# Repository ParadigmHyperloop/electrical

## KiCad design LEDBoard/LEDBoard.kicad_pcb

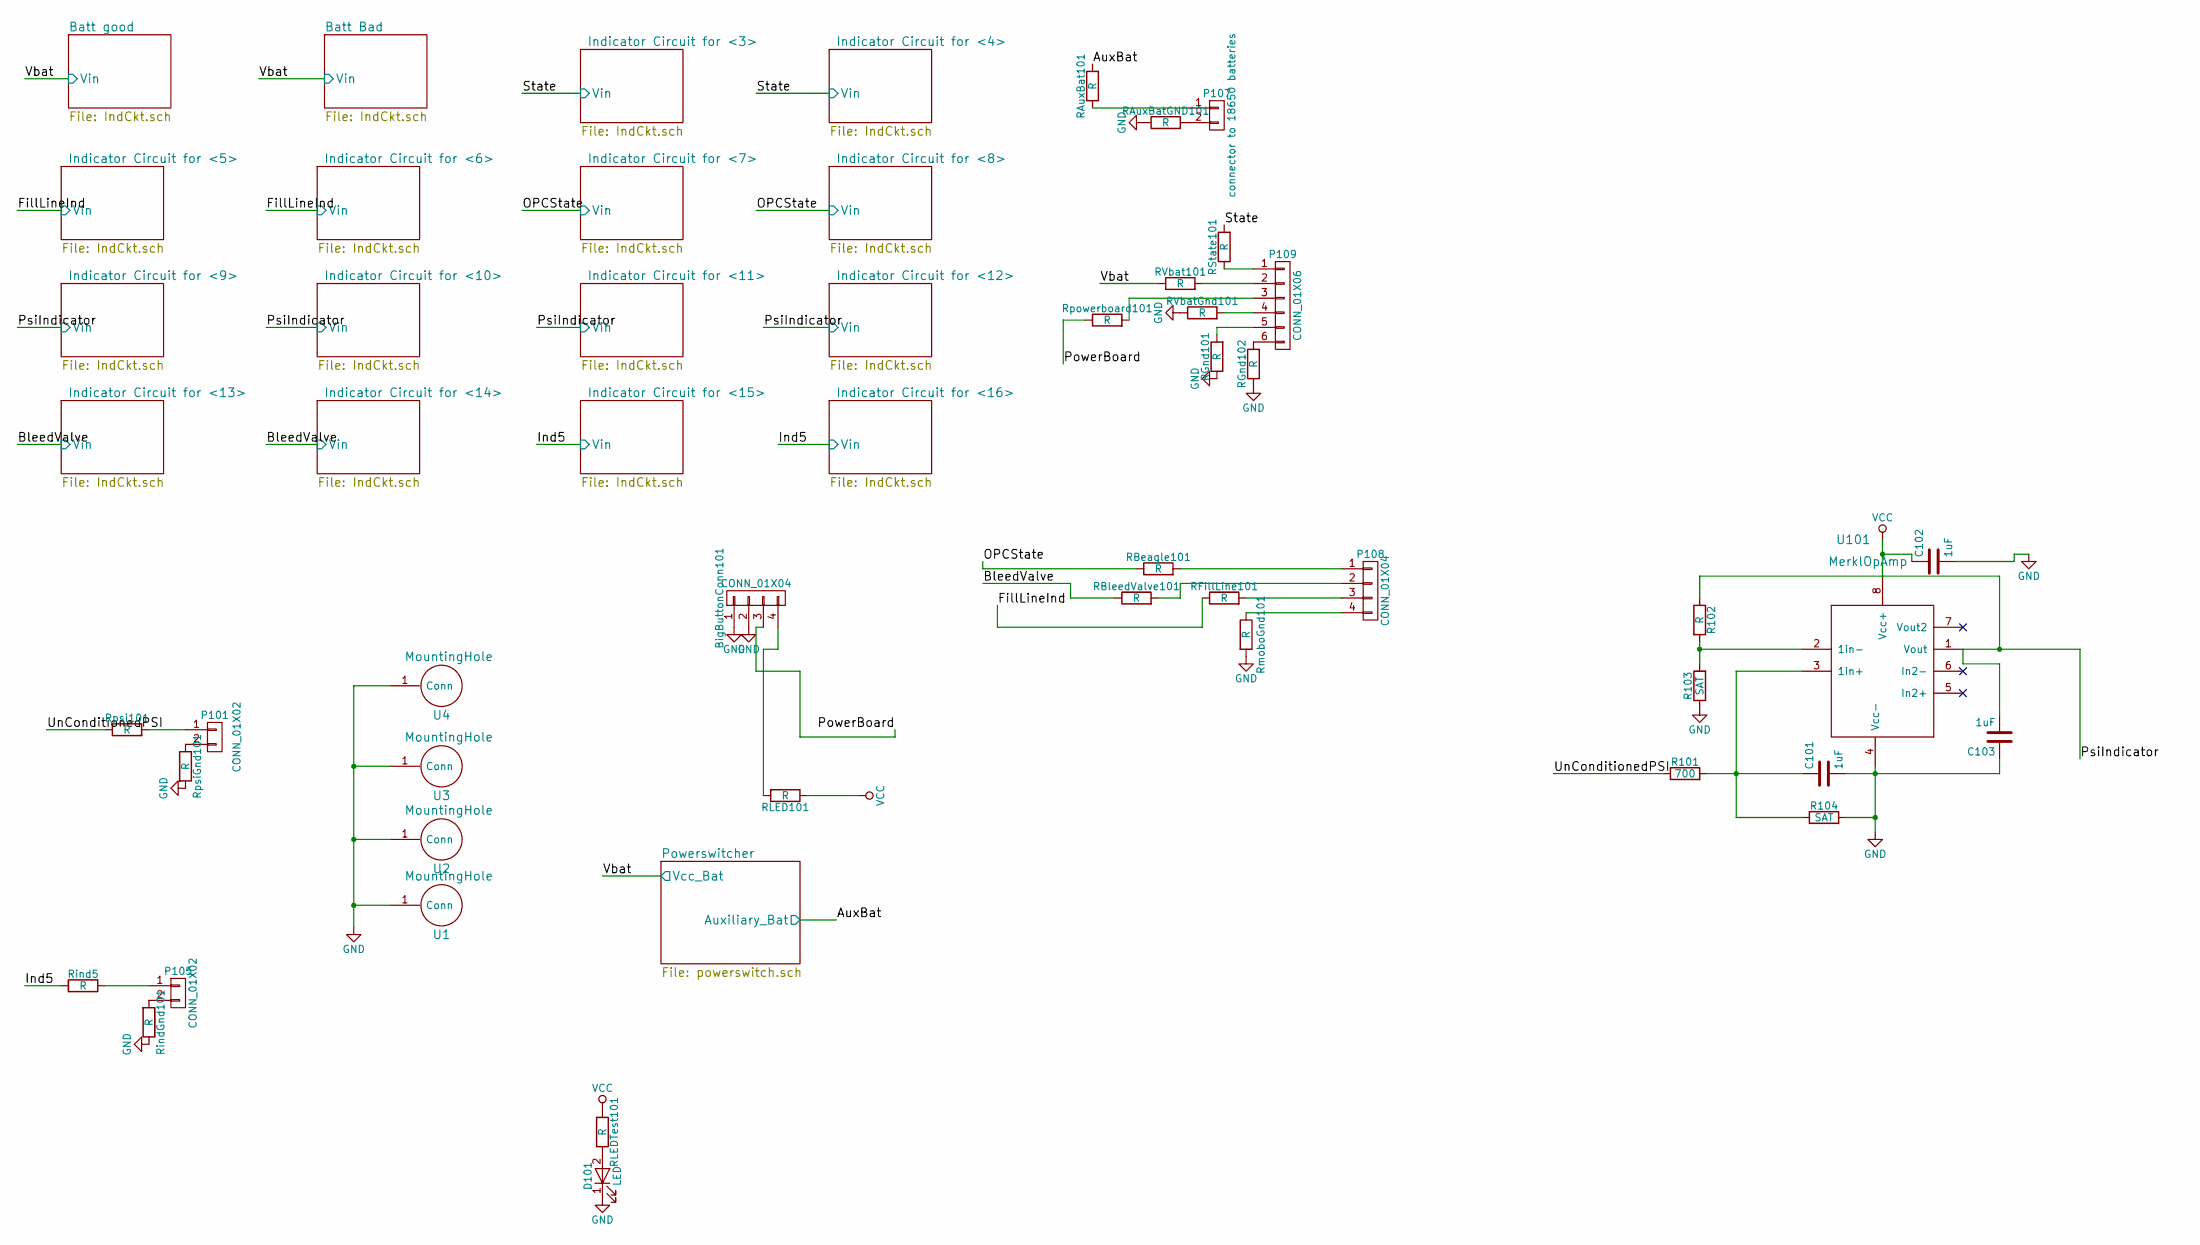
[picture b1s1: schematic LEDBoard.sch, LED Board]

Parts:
BigButtonConn101: CONN_01X04; CONN_PHOENIX_1844236_4PIN_1
C101, C102, C103: 1uF; C_1206_HandSoldering
D101: LED; LED_1206
P101: CONN_01X02; CONN_PHOENIX_1844210_2PIN_1
P105: CONN_01X02; CONN_PHOENIX_1844210_2PIN
P107: connector to 18650 batteries; CONN_PHOENIX_1844210_2PIN
P108: CONN_01X04; CONN_PHOENIX_1844236_4PIN_1
P109: CONN_01X06; CONN_PHOENIX_1844252_6PIN
R101: 700; R_1206_HandSoldering
R102: R; R_1206_HandSoldering
R103, R104: SAT; R_1206_HandSoldering
RAuxBat101: R; R_1206_HandSoldering
RAuxBatGND101: R; R_1206_HandSoldering
RBeagle101: R; R_1206_HandSoldering
RBleedValve101: R; R_1206_HandSoldering
RFillLine101: R; R_1206_HandSoldering
RGnd101, RGnd102: R; R_1206_HandSoldering
RLED101: R; R_1206_HandSoldering
RLEDTest101: R; R_1206_HandSoldering
RState101: R; R_1206_HandSoldering
RVbat101: R; R_1206_HandSoldering
RVbatGnd101: R; R_1206_HandSoldering
Rind5: R; R_1206_HandSoldering
RindGnd101: R; R_1206_HandSoldering
RmoboGnd101: R; R_1206_HandSoldering
Rpowerboard101: R; R_1206_HandSoldering
Rpsi101: R; R_1206_HandSoldering
RpsiGnd101: R; R_1206_HandSoldering
U1, U2, U3, U4: MountingHole; MountingHole_5.5mm_Pad_Via
U101: MerklOpAmp; SOIC-8_3.9x4.9mm_Pitch1.27mm

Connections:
/AuxBat: RAuxBat101.2; also elsewhere on the board
/BleedValve: RBleedValve101.1; also elsewhere on the board
/FillLineInd: RFillLine101.1; also elsewhere on the board
/Ind5: Rind5.2; also elsewhere on the board
/OPCState: RBeagle101.1; also elsewhere on the board
/PowerBoard: BigButtonConn101.3, Rpowerboard101.1
/PsiIndicator: C103.2, R102.1, U101.1 (Vout); also elsewhere on the board
/State: RState101.2; also elsewhere on the board
/UnConditionedPSI: R101.1, Rpsi101.1
/Vbat: RVbat101.1; also elsewhere on the board
GND: BigButtonConn101.1, BigButtonConn101.2, C101.2, C102.2, C103.1, D101.1 (K), R103.1, R104.2, RAuxBatGND101.1, RGnd101.1, RGnd102.1, RVbatGnd101.1, RindGnd101.1, RmoboGnd101.2, RpsiGnd101.2, U1.1, U2.1, U3.1, U4.1, U101.4 (Vcc-); also elsewhere on the board
unnamed: BigButtonConn101.4, RLED101.2
unnamed: C101.1, R101.2, R104.1, U101.3 (1in+)
unnamed 65: D101.2 (A), RLEDTest101.1; also elsewhere on the board
unnamed: P101.1, Rpsi101.2
unnamed: P101.2, RpsiGnd101.1
unnamed: P105.1, Rind5.1
unnamed: P105.2, RindGnd101.2
unnamed: P107.1, RAuxBat101.1
unnamed: P107.2, RAuxBatGND101.2
unnamed: P108.1, RBeagle101.2
unnamed: P108.2, RBleedValve101.2
unnamed: P108.3, RFillLine101.2
unnamed 107: P108.4, RmoboGnd101.1; also elsewhere on the board
unnamed: P109.1, RState101.1
unnamed: P109.2, RVbat101.2
unnamed: P109.3, Rpowerboard101.2
unnamed: P109.4, RVbatGnd101.2
unnamed: P109.5, RGnd101.2
unnamed: P109.6, RGnd102.2
unnamed: R102.2, R103.2, U101.2 (1in-)
VCC: C102.1, RLED101.1, RLEDTest101.2, U101.8 (Vcc+); also elsewhere on the board

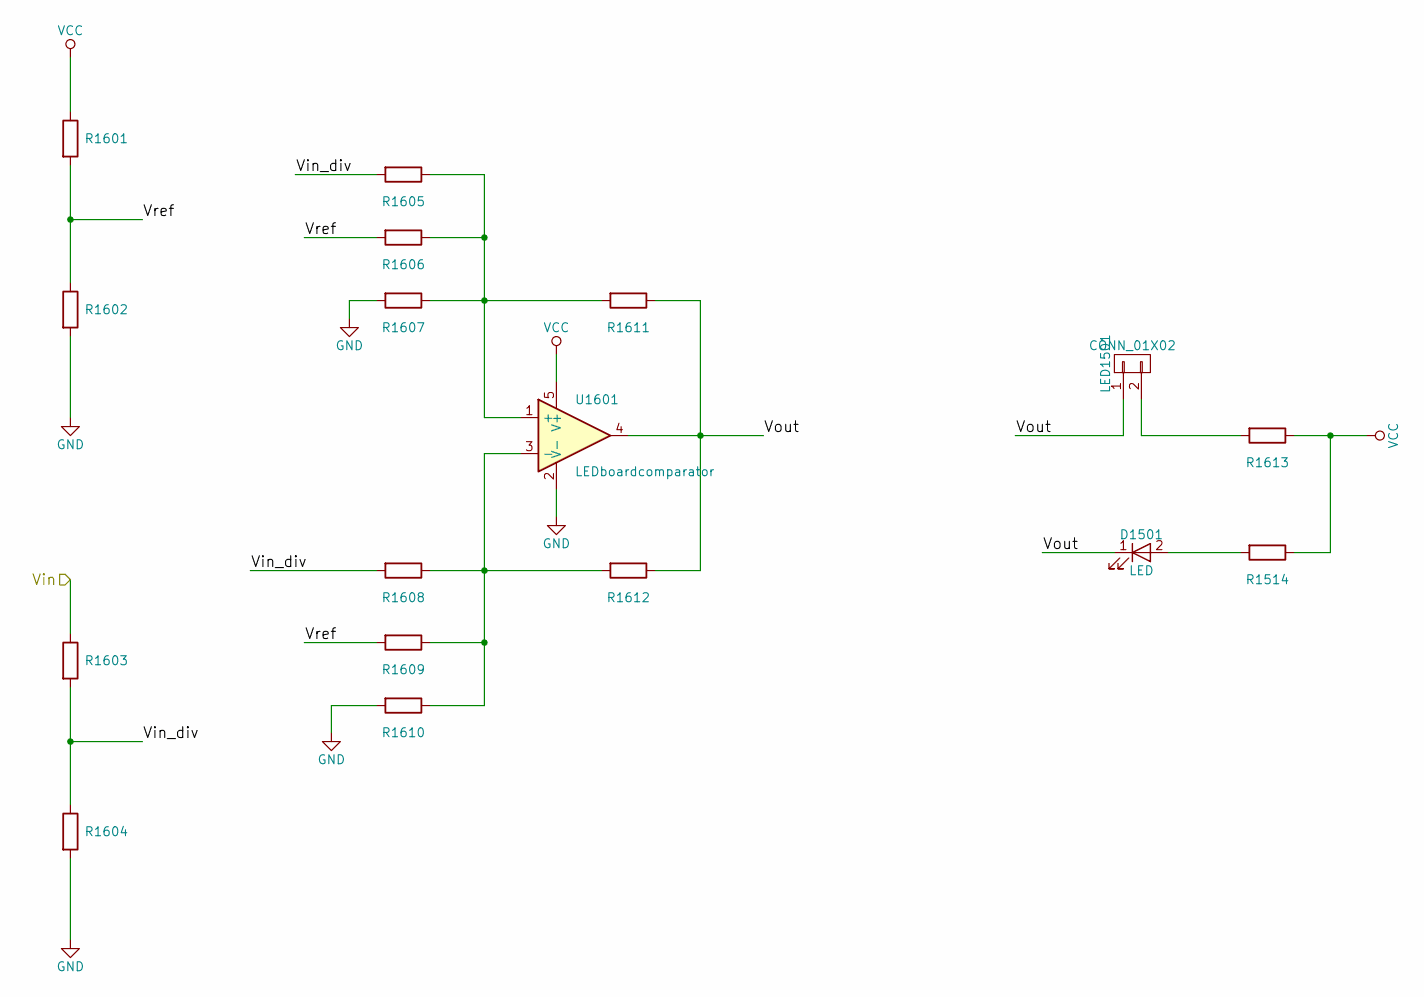
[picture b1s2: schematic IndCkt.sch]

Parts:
D1601: LED; LED_0805
LED201: CONN_01X02; CONN_PHOENIX_1844210_2PIN_1
R201, R202, R203, R204, R205, R206, R207, R208, R209, R210, R211, R212, R213, R1614: R; R_1206_HandSoldering
U201: LEDboardcomparator; SOT-23-5

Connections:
/Batt good/Vin_div: R203.2, R204.1, R205.2, R208.2
/Batt good/Vout: LED201.1, R211.1, R212.1, U201.4; also elsewhere on the board
/Batt good/Vref: R201.2, R202.1, R206.2, R209.2
/Vbat: R203.1; also elsewhere on the board
GND: R202.2, R204.2, R207.2, R210.2, U201.2 (V-); also elsewhere on the board
unnamed 80: R1614.2; also elsewhere on the board
unnamed: LED201.2, R213.2
unnamed: R205.1, R206.1, R207.1, R211.2, U201.1 (+)
unnamed: R208.1, R209.1, R210.1, R212.2, U201.3 (-)
VCC: R201.1, R213.1, R1614.1, U201.5 (V+); also elsewhere on the board

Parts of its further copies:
D201, D301, D401, D501, D601, D701, D801, D901, D1001, D1101, D1201, D1301, D1401, D1501, D1801: LED; LED_0805
LED301, LED401, LED501, LED601, LED701, LED801, LED901, LED1001, LED1101, LED1201, LED1301, LED1401, LED1501, LED1601, LED1801: CONN_01X02; CONN_PHOENIX_1844210_2PIN_1
R214, R301, R302, R303, R304, R305, R306, R307, R308, R309, R310, R311, R312, R313, R314, R401, R402, R403, R404, R405, R406, R407, R408, R409, R410, R411, R412, R413, R414, R501, R502, R503, R504, R505, R506, R507, R508, R509, R510, R511, R512, R513, R514, R601, R602, R603, R604, R605, R606, R607, R608, R609, R610, R611, R612, R613, R614, R701, R702, R703, R704, R705, R706, R707, R708, R709, R710, R711, R712, R713, R714, R801, R802, R803, R804, R805, R806, R807, R808, R809, R810, R811, R812, R813, R814, R901, R902, R903, R904, R905, R906, R907, R908, R909, R910, R911, R912, R913, R914, R1001, R1002, R1003, R1004, R1005, R1006, R1007, R1008, R1009, R1010, R1011, R1012, R1013, R1014, R1101, R1102, R1103, R1104, R1105, R1106, R1107, R1108, R1109, R1110, R1111, R1112, R1113, R1114, R1201, R1202, R1203, R1204, R1205, R1206, R1207, R1208, R1209, R1210, R1211, R1212, R1213, R1214, R1301, R1302, R1303, R1304, R1305, R1306, R1307, R1308, R1309, R1310, R1311, R1312, R1313, R1314, R1401, R1402, R1403, R1404, R1405, R1406, R1407, R1408, R1409, R1410, R1411, R1412, R1413, R1414, R1501, R1502, R1503, R1504, R1505, R1506, R1507, R1508, R1509, R1510, R1511, R1512, R1513, R1514, R1601, R1602, R1603, R1604, R1605, R1606, R1607, R1608, R1609, R1610, R1611, R1612, R1613, R1701, R1702, R1703, R1704, R1705, R1706, R1707, R1708, R1709, R1710, R1711, R1712, R1713, R1805: R; R_1206_HandSoldering
U301, U401, U501, U601, U701, U801, U901, U1001, U1101, U1201, U1301, U1401, U1501, U1601, U1701: LEDboardcomparator; SOT-23-5

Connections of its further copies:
/ Indicator Circuit for <3>/Vin_div: R1003.2, R1004.1, R1005.2, R1008.2
/ Indicator Circuit for <3>/Vout: LED1001.1, R1011.1, R1012.1, U1001.4; also elsewhere on the board
/ Indicator Circuit for <3>/Vref: R1001.2, R1002.1, R1006.2, R1009.2
/ Indicator Circuit for <4>/Vin_div: R1403.2, R1404.1, R1405.2, R1408.2
/ Indicator Circuit for <4>/Vout: LED1301.1, R1411.1, R1412.1, U1401.4; also elsewhere on the board
/ Indicator Circuit for <4>/Vref: R1401.2, R1402.1, R1406.2, R1409.2
/ Indicator Circuit for <5>/Vin_div: R303.2, R304.1, R305.2, R308.2
/ Indicator Circuit for <5>/Vout: LED301.1, R311.1, R312.1, U301.4; also elsewhere on the board
/ Indicator Circuit for <5>/Vref: R301.2, R302.1, R306.2, R309.2
/ Indicator Circuit for <6>/Vin_div: R703.2, R704.1, R705.2, R708.2
/ Indicator Circuit for <6>/Vout: LED701.1, R711.1, R712.1, U701.4; also elsewhere on the board
/ Indicator Circuit for <6>/Vref: R701.2, R702.1, R706.2, R709.2
/ Indicator Circuit for <7>/Vin_div: R1103.2, R1104.1, R1105.2, R1108.2
/ Indicator Circuit for <7>/Vout: LED1101.1, R1111.1, R1112.1, U1101.4; also elsewhere on the board
/ Indicator Circuit for <7>/Vref: R1101.2, R1102.1, R1106.2, R1109.2
/ Indicator Circuit for <8>/Vin_div: R1503.2, R1504.1, R1505.2, R1508.2
/ Indicator Circuit for <8>/Vout: LED1401.1, R1511.1, R1512.1, U1501.4; also elsewhere on the board
/ Indicator Circuit for <8>/Vref: R1501.2, R1502.1, R1506.2, R1509.2
/ Indicator Circuit for <9>/Vin_div: R403.2, R404.1, R405.2, R408.2
/ Indicator Circuit for <9>/Vout: LED401.1, R411.1, R412.1, U401.4; also elsewhere on the board
/ Indicator Circuit for <9>/Vref: R401.2, R402.1, R406.2, R409.2
/ Indicator Circuit for <10>/Vin_div: R803.2, R804.1, R805.2, R808.2
/ Indicator Circuit for <10>/Vout: LED801.1, R811.1, R812.1, U801.4; also elsewhere on the board
/ Indicator Circuit for <10>/Vref: R801.2, R802.1, R806.2, R809.2
/ Indicator Circuit for <11>/Vin_div: R1203.2, R1204.1, R1205.2, R1208.2
/ Indicator Circuit for <11>/Vout: LED1801.1, R1211.1, R1212.1, U1201.4; also elsewhere on the board
/ Indicator Circuit for <11>/Vref: R1201.2, R1202.1, R1206.2, R1209.2
/ Indicator Circuit for <12>/Vin_div: R1603.2, R1604.1, R1605.2, R1608.2
/ Indicator Circuit for <12>/Vout: LED1501.1, R1611.1, R1612.1, U1601.4; also elsewhere on the board
/ Indicator Circuit for <12>/Vref: R1601.2, R1602.1, R1606.2, R1609.2
/ Indicator Circuit for <13>/Vin_div: R503.2, R504.1, R505.2, R508.2
/ Indicator Circuit for <13>/Vout: LED501.1, R511.1, R512.1, U501.4; also elsewhere on the board
/ Indicator Circuit for <13>/Vref: R501.2, R502.1, R506.2, R509.2
/ Indicator Circuit for <14>/Vin_div: R903.2, R904.1, R905.2, R908.2
/ Indicator Circuit for <14>/Vout: LED901.1, R911.1, R912.1, U901.4; also elsewhere on the board
/ Indicator Circuit for <14>/Vref: R901.2, R902.1, R906.2, R909.2
/ Indicator Circuit for <15>/Vin_div: R1303.2, R1304.1, R1305.2, R1308.2
/ Indicator Circuit for <15>/Vout: LED1201.1, R1311.1, R1312.1, U1301.4; also elsewhere on the board
/ Indicator Circuit for <15>/Vref: R1301.2, R1302.1, R1306.2, R1309.2
/ Indicator Circuit for <16>/Vin_div: R1703.2, R1704.1, R1705.2, R1708.2
/ Indicator Circuit for <16>/Vout: LED1601.1, R1711.1, R1712.1, U1701.4; also elsewhere on the board
/ Indicator Circuit for <16>/Vref: R1701.2, R1702.1, R1706.2, R1709.2
/Batt Bad/Vin_div: R603.2, R604.1, R605.2, R608.2
/Batt Bad/Vout: LED601.1, R611.1, R612.1, U601.4; also elsewhere on the board
/Batt Bad/Vref: R601.2, R602.1, R606.2, R609.2
/BleedValve: R503.1, R903.1; also elsewhere on the board
/FillLineInd: R303.1, R703.1; also elsewhere on the board
/Ind5: R1303.1, R1703.1; also elsewhere on the board
/OPCState: R1103.1, R1503.1; also elsewhere on the board
/PsiIndicator: R403.1, R803.1, R1203.1, R1603.1; also elsewhere on the board
/State: R1003.1, R1403.1; also elsewhere on the board
/Vbat: R603.1; also elsewhere on the board
GND: R302.2, R304.2, R307.2, R310.2, R402.2, R404.2, R407.2, R410.2, R502.2, R504.2, R507.2, R510.2, R602.2, R604.2, R607.2, R610.2, R702.2, R704.2, R707.2, R710.2, R802.2, R804.2, R807.2, R810.2, R902.2, R904.2, R907.2, R910.2, R1002.2, R1004.2, R1007.2, R1010.2, R1102.2, R1104.2, R1107.2, R1110.2, R1202.2, R1204.2, R1207.2, R1210.2, R1302.2, R1304.2, R1307.2, R1310.2, R1402.2, R1404.2, R1407.2, R1410.2, R1502.2, R1504.2, R1507.2, R1510.2, R1602.2, R1604.2, R1607.2, R1610.2, R1702.2, R1704.2, R1707.2, R1710.2, U301.2 (V-), U401.2 (V-), U501.2 (V-), U601.2 (V-), U701.2 (V-), U801.2 (V-), U901.2 (V-), U1001.2 (V-), U1101.2 (V-), U1201.2 (V-), U1301.2 (V-), U1401.2 (V-), U1501.2 (V-), U1601.2 (V-), U1701.2 (V-); also elsewhere on the board
unnamed 66: R214.2; also elsewhere on the board
unnamed 67: R314.2; also elsewhere on the board
unnamed 68: R414.2; also elsewhere on the board
unnamed 69: R514.2; also elsewhere on the board
unnamed 70: R614.2; also elsewhere on the board
unnamed 71: R714.2; also elsewhere on the board
unnamed 72: R814.2; also elsewhere on the board
unnamed 73: R914.2; also elsewhere on the board
unnamed 74: R1014.2; also elsewhere on the board
unnamed 75: R1114.2; also elsewhere on the board
unnamed 76: R1214.2; also elsewhere on the board
unnamed 77: R1314.2; also elsewhere on the board
unnamed 78: R1414.2; also elsewhere on the board
unnamed 79: R1514.2; also elsewhere on the board
unnamed 81: R1805.2; also elsewhere on the board
unnamed: LED301.2, R313.2
unnamed: LED401.2, R413.2
unnamed: LED501.2, R513.2
unnamed: LED601.2, R613.2
unnamed: LED701.2, R713.2
unnamed: LED801.2, R813.2
unnamed: LED901.2, R913.2
unnamed: LED1001.2, R1013.2
unnamed: LED1101.2, R1113.2
unnamed: LED1201.2, R1313.2
unnamed: LED1301.2, R1413.2
unnamed: LED1401.2, R1513.2
unnamed: LED1501.2, R1613.2
unnamed: LED1601.2, R1713.2
unnamed: LED1801.2, R1213.2
unnamed: R305.1, R306.1, R307.1, R311.2, U301.1 (+)
unnamed: R308.1, R309.1, R310.1, R312.2, U301.3 (-)
unnamed: R405.1, R406.1, R407.1, R411.2, U401.1 (+)
unnamed: R408.1, R409.1, R410.1, R412.2, U401.3 (-)
unnamed: R505.1, R506.1, R507.1, R511.2, U501.1 (+)
unnamed: R508.1, R509.1, R510.1, R512.2, U501.3 (-)
unnamed: R605.1, R606.1, R607.1, R611.2, U601.1 (+)
unnamed: R608.1, R609.1, R610.1, R612.2, U601.3 (-)
unnamed: R705.1, R706.1, R707.1, R711.2, U701.1 (+)
unnamed: R708.1, R709.1, R710.1, R712.2, U701.3 (-)
unnamed: R805.1, R806.1, R807.1, R811.2, U801.1 (+)
unnamed: R808.1, R809.1, R810.1, R812.2, U801.3 (-)
unnamed: R905.1, R906.1, R907.1, R911.2, U901.1 (+)
unnamed: R908.1, R909.1, R910.1, R912.2, U901.3 (-)
unnamed: R1005.1, R1006.1, R1007.1, R1011.2, U1001.1 (+)
unnamed: R1008.1, R1009.1, R1010.1, R1012.2, U1001.3 (-)
unnamed: R1105.1, R1106.1, R1107.1, R1111.2, U1101.1 (+)
unnamed: R1108.1, R1109.1, R1110.1, R1112.2, U1101.3 (-)
unnamed: R1205.1, R1206.1, R1207.1, R1211.2, U1201.1 (+)
unnamed: R1208.1, R1209.1, R1210.1, R1212.2, U1201.3 (-)
unnamed: R1305.1, R1306.1, R1307.1, R1311.2, U1301.1 (+)
unnamed: R1308.1, R1309.1, R1310.1, R1312.2, U1301.3 (-)
unnamed: R1405.1, R1406.1, R1407.1, R1411.2, U1401.1 (+)
unnamed: R1408.1, R1409.1, R1410.1, R1412.2, U1401.3 (-)
unnamed: R1505.1, R1506.1, R1507.1, R1511.2, U1501.1 (+)
unnamed: R1508.1, R1509.1, R1510.1, R1512.2, U1501.3 (-)
unnamed: R1605.1, R1606.1, R1607.1, R1611.2, U1601.1 (+)
unnamed: R1608.1, R1609.1, R1610.1, R1612.2, U1601.3 (-)
unnamed: R1705.1, R1706.1, R1707.1, R1711.2, U1701.1 (+)
unnamed: R1708.1, R1709.1, R1710.1, R1712.2, U1701.3 (-)
VCC: R214.1, R301.1, R313.1, R314.1, R401.1, R413.1, R414.1, R501.1, R513.1, R514.1, R601.1, R613.1, R614.1, R701.1, R713.1, R714.1, R801.1, R813.1, R814.1, R901.1, R913.1, R914.1, R1001.1, R1013.1, R1014.1, R1101.1, R1113.1, R1114.1, R1201.1, R1213.1, R1214.1, R1301.1, R1313.1, R1314.1, R1401.1, R1413.1, R1414.1, R1501.1, R1513.1, R1514.1, R1601.1, R1613.1, R1701.1, R1713.1, R1805.1, U301.5 (V+), U401.5 (V+), U501.5 (V+), U601.5 (V+), U701.5 (V+), U801.5 (V+), U901.5 (V+), U1001.5 (V+), U1101.5 (V+), U1201.5 (V+), U1301.5 (V+), U1401.5 (V+), U1501.5 (V+), U1601.5 (V+), U1701.5 (V+); also elsewhere on the board

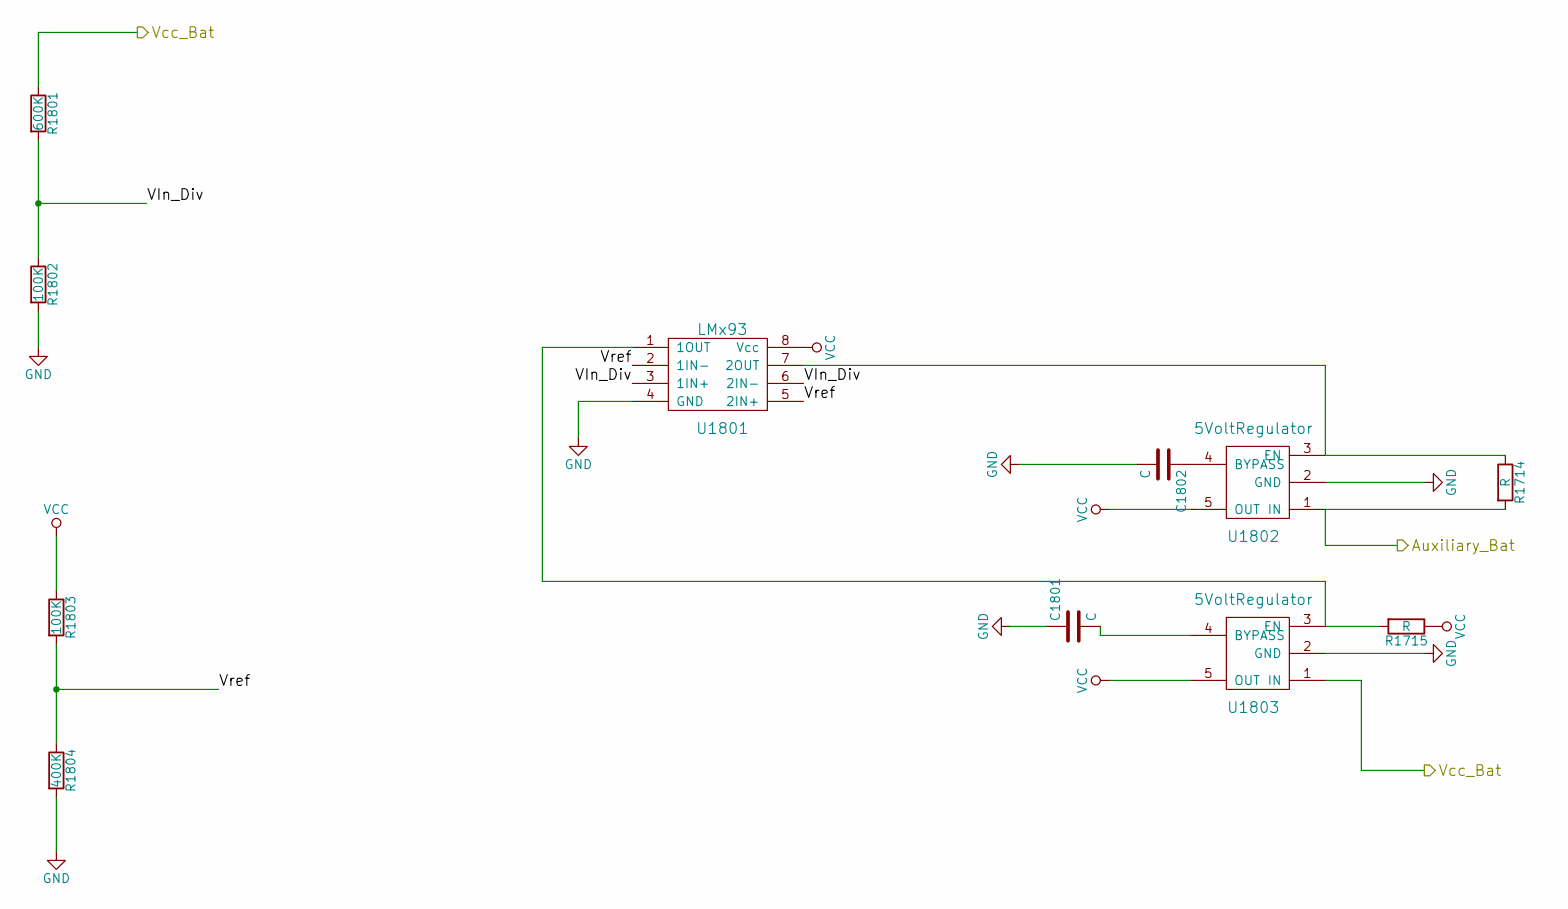
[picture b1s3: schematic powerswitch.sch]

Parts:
C1801, C1802: C; C_1206_HandSoldering
R1714, R1715: R; R_1206_HandSoldering
R1801: 600K; R_1206_HandSoldering
R1802, R1803: 100K; R_1206_HandSoldering
R1804: 400K; R_1206_HandSoldering
U1801: LMx93; SOIC-8_3.9x4.9mm_Pitch1.27mm
U1802, U1803: 5VoltRegulator; SOT-23-6_Handsoldering

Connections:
/AuxBat: R1714.2, U1802.1 (IN); also elsewhere on the board
/Powerswitcher/VIn_Div: R1801.2, R1802.1, U1801.3 (1IN+), U1801.6 (2IN-)
/Powerswitcher/Vref: R1803.2, R1804.1, U1801.2 (1IN-), U1801.5 (2IN+)
/Vbat: R1801.1, U1803.1 (IN); also elsewhere on the board
GND: C1801.1, C1802.2, R1802.2, R1804.2, U1801.4 (GND), U1802.2 (GND), U1803.2 (GND); also elsewhere on the board
unnamed: C1801.2, U1803.4 (BYPASS)
unnamed: C1802.1, U1802.4 (BYPASS)
unnamed: R1714.1, U1801.7 (2OUT), U1802.3 (EN)
unnamed: R1715.2, U1801.1 (1OUT), U1803.3 (EN)
VCC: R1715.1, R1803.1, U1801.8 (Vcc), U1802.5 (OUT), U1803.5 (OUT); also elsewhere on the board

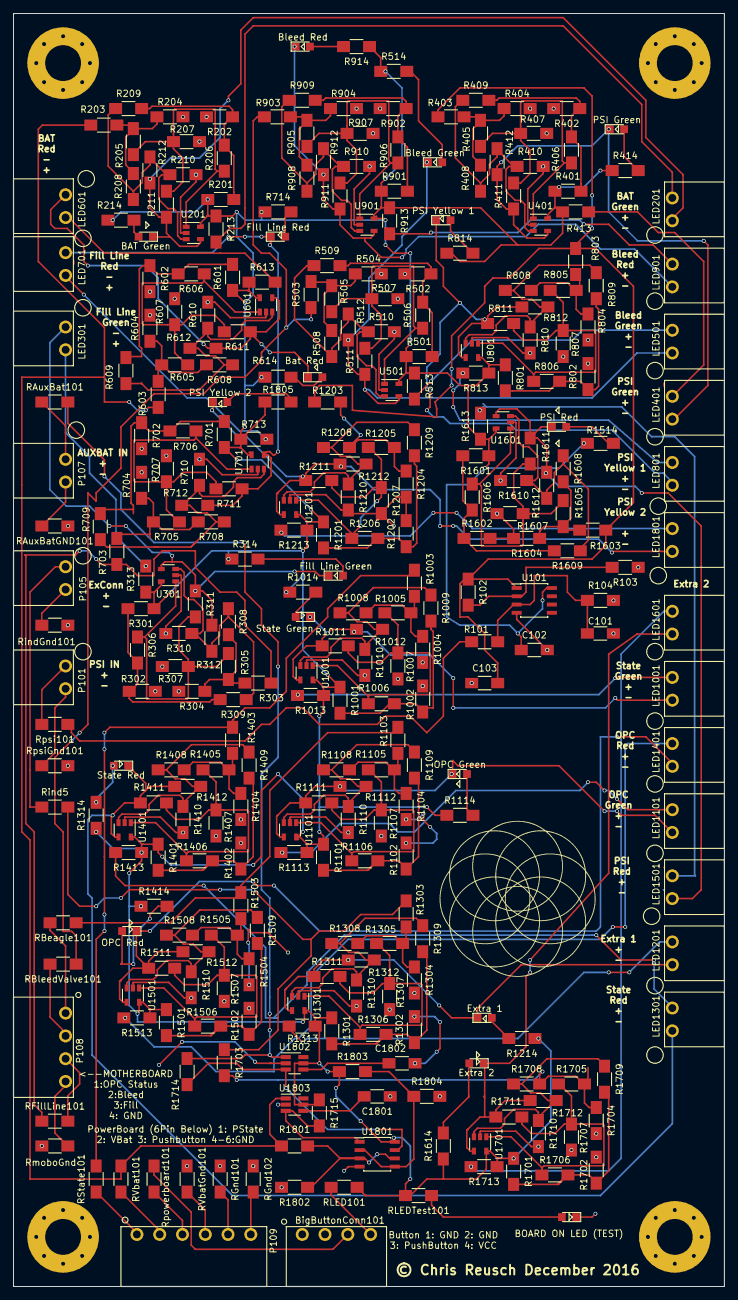
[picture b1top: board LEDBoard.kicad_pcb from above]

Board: 2 copper layers, 109.2 x 195.6 mm, 320 parts (0 on the bottom side), 150 nets.

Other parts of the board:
BAT Green: LED; LED_0805
BOARD ON LED (TEST): LED; LED_0805
Bat Red: LED; LED_0805
Bleed Green: LED; LED_0805
Bleed Red: LED; LED_0805
Extra 1, Extra 2: LED; LED_0805
FIll Line Red: LED; LED_0805
Fill Line Green: LED; LED_0805
OPC Green: LED; LED_0805
OPC Red: LED; LED_0805
PSI Green: LED; LED_0805
PSI Red: LED; LED_0805
PSI Yellow 1, PSI Yellow 2: LED; LED_0805
RmoboGnd: R; R_1206_HandSoldering
State Green: LED; LED_0805
State Red: LED; LED_0805

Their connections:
/ Indicator Circuit for <3>/Vout: State Green.1; also elsewhere on the board
/ Indicator Circuit for <4>/Vout: State Red.1; also elsewhere on the board
/ Indicator Circuit for <5>/Vout: Fill Line Green.1; also elsewhere on the board
/ Indicator Circuit for <6>/Vout: FIll Line Red.1; also elsewhere on the board
/ Indicator Circuit for <7>/Vout: OPC Green.1; also elsewhere on the board
/ Indicator Circuit for <8>/Vout: OPC Red.1; also elsewhere on the board
/ Indicator Circuit for <9>/Vout: PSI Green.1; also elsewhere on the board
/ Indicator Circuit for <10>/Vout: PSI Yellow 1.1; also elsewhere on the board
/ Indicator Circuit for <11>/Vout: PSI Yellow 2.1; also elsewhere on the board
/ Indicator Circuit for <12>/Vout: PSI Red.1; also elsewhere on the board
/ Indicator Circuit for <13>/Vout: Bleed Green.1; also elsewhere on the board
/ Indicator Circuit for <14>/Vout: Bleed Red.1; also elsewhere on the board
/ Indicator Circuit for <15>/Vout: Extra 1.1; also elsewhere on the board
/ Indicator Circuit for <16>/Vout: Extra 2.1; also elsewhere on the board
/Batt Bad/Vout: Bat Red.1; also elsewhere on the board
/Batt good/Vout: BAT Green.1; also elsewhere on the board
GND: BOARD ON LED (TEST).1, RmoboGnd.2; also elsewhere on the board
unnamed 65: BOARD ON LED (TEST).2; also elsewhere on the board
unnamed 66: BAT Green.2; also elsewhere on the board
unnamed 67: Fill Line Green.2; also elsewhere on the board
unnamed 68: PSI Green.2; also elsewhere on the board
unnamed 69: Bleed Green.2; also elsewhere on the board
unnamed 70: Bat Red.2; also elsewhere on the board
unnamed 71: FIll Line Red.2; also elsewhere on the board
unnamed 72: PSI Yellow 1.2; also elsewhere on the board
unnamed 73: Bleed Red.2; also elsewhere on the board
unnamed 74: State Green.2; also elsewhere on the board
unnamed 75: OPC Green.2; also elsewhere on the board
unnamed 76: Extra 1.2; also elsewhere on the board
unnamed 77: State Red.2; also elsewhere on the board
unnamed 78: OPC Red.2; also elsewhere on the board
unnamed 79: PSI Red.2; also elsewhere on the board
unnamed 80: Extra 2.2; also elsewhere on the board
unnamed 81: PSI Yellow 2.2; also elsewhere on the board
unnamed 107: RmoboGnd.1; also elsewhere on the board

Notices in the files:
LEDBoard/LEDBoard.kicad_pcb:
© Chris Reusch December 2016
MainPowerBoard/MainPowerBoard.kicad_pcb:
© Paradigm 2017
MotherBoard/Motherboard.kicad_pcb:
© Paradigm 2016
parts and their libraries:
Copyright 2016 Accelerated Designs. All rights reserved.
